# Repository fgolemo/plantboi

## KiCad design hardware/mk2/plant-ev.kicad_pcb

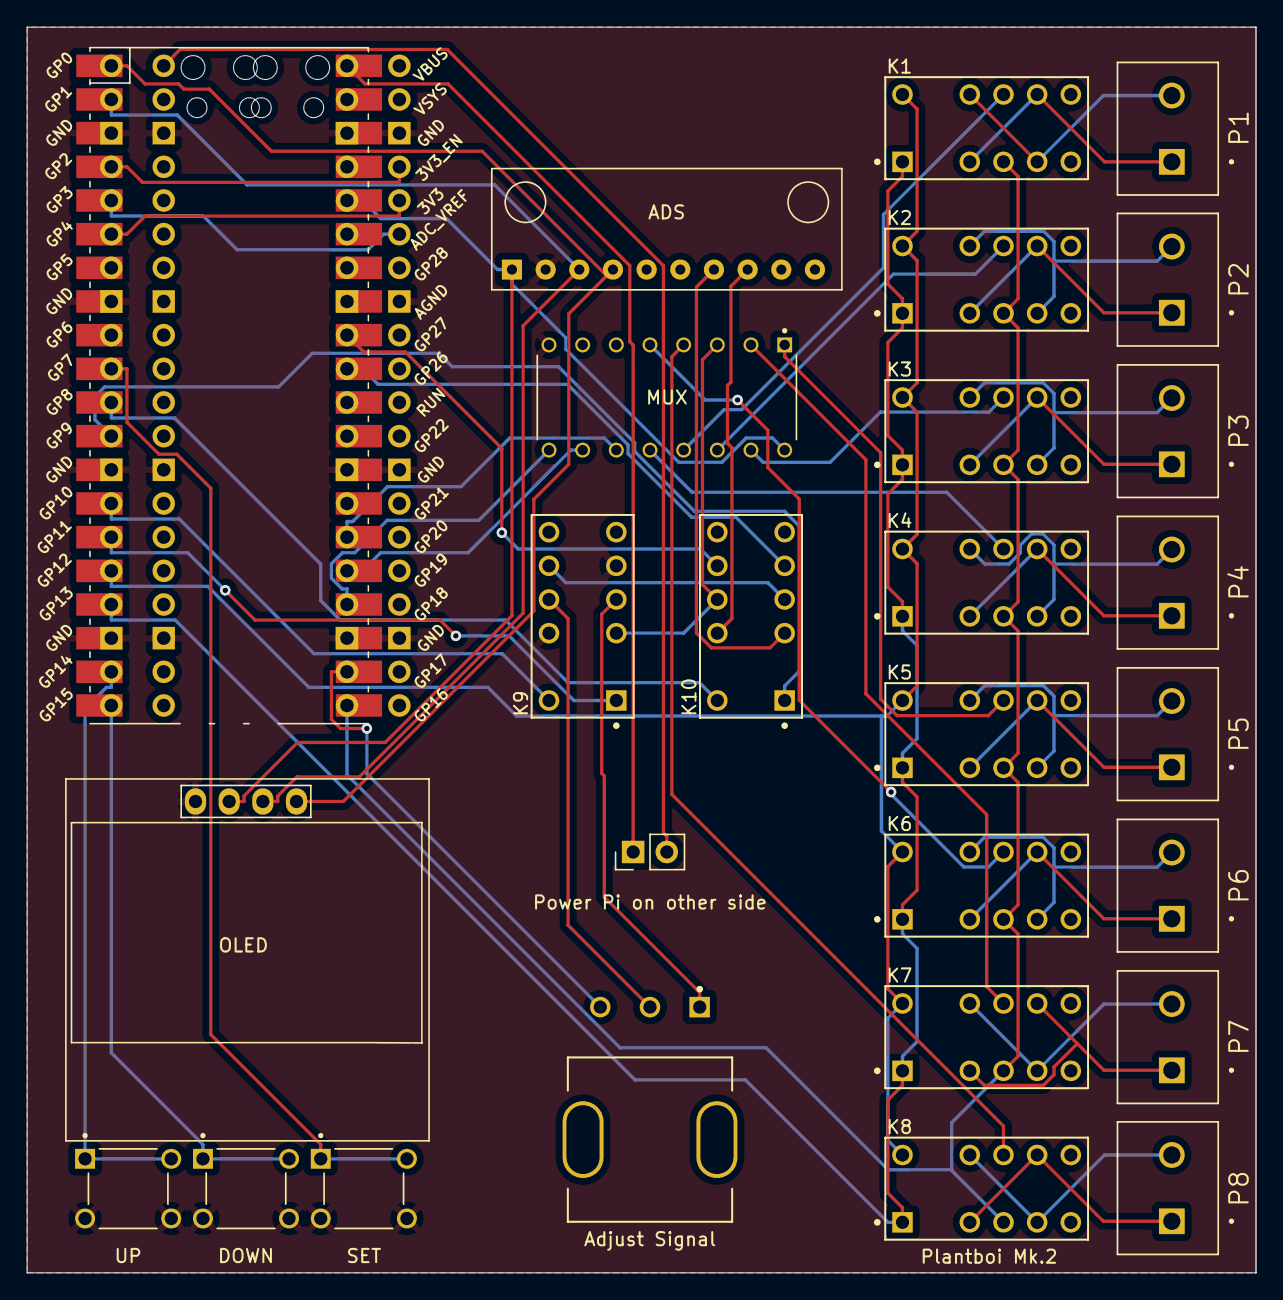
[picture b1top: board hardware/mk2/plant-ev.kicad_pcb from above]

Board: 2 copper layers, 92.7 x 94.0 mm, 28 parts (1 on the bottom side), 55 nets.

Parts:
ADS: ADS1115_ADC_Module; ADC1115_ADC_Module
Adjust Signal: PDB12-H4301-105BF; Bourns-PDB12-H4301-105BF-0
DOWN: TS02-66-120-BK-160-LCR-D; SW_TS02-66-120-BK-160-LCR-D
K1, K2, K3, K4, K5, K6, K7, K8, K9, K10: TXS2-L-3V; Panasonic-TXS2-L-3V-MFG
MUX: CD74HC4051E; DIP794W45P254L1969H508Q16
OLED: SSD1306; 128x64OLED
P1, P2, P3, P4, P5, P6, P7, P8: TB002-500-02BE; CUI_TB002-500-02BE
Power Pi on other side: Jumper_2_Open; PinHeader_1x02_P2.54mm_Vertical
SET: TS02-66-120-BK-160-LCR-D; SW_TS02-66-120-BK-160-LCR-D
U1: Pico influx; RPi_Pico_SMD_TH_NOGVE
U2: Pico sensor; RPi_Pico_SMD_TH_NOGVE
UP: TS02-66-120-BK-160-LCR-D; SW_TS02-66-120-BK-160-LCR-D

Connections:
/3V: ADS.1 (VCC), MUX.16 (VCC), OLED.2 (VCC), U2.36 (3V3)
/ADC1: K10.5, U2.31 (GPIO26_ADC0)
/ADC2: K10.8, U2.32 (GPIO27_ADC1)
/GND: ADS.2 (GND), DOWN.3, DOWN.4, K9.5, K9.10, MUX.8 (GND), OLED.1 (GND), SET.3, SET.4, U1.3 (GND), U1.8 (GND), U1.13 (GND), U1.18 (GND), U1.23 (GND), U1.28 (GND), U1.38 (GND), U2.3 (GND), U2.8 (GND), U2.13 (GND), U2.18 (GND), U2.23 (GND), U2.28 (GND), U2.38 (GND), UP.3, UP.4
/MUX0: MUX.11 (S0), U2.26 (GPIO20)
/MUX1: MUX.10 (S1), U2.25 (GPIO19)
/MUX2: MUX.9 (S2), U2.24 (GPIO18)
/POTP: Adjust Signal.3, U2.22 (GPIO17)
/PRBE: K1.4, K2.4, K3.4, K4.4, K5.4, K6.4, K7.4, K8.4, U2.21 (GPIO16)
/R1M: K1.1 (SET+), K2.1 (SET+), K3.1 (SET+), K4.1 (SET+), K5.1 (SET+), K6.1 (SET+), K7.1 (SET+), K8.1 (SET+), U2.17 (GPIO13)
/R1P: K1.12 (RESET+), K2.12 (RESET+), K3.12 (RESET+), K4.12 (RESET+), K5.12 (RESET+), K6.12 (RESET+), K7.12 (RESET+), K8.12 (RESET+), U2.16 (GPIO12)
/R2M: K9.1 (SET+), U2.15 (GPIO11)
/R2P: K9.12 (RESET+), U2.14 (GPIO10)
/R3M: K10.1 (SET+), U2.12 (GPIO9)
/R3P: K10.12 (RESET+), U2.11 (GPIO8)
/SCL: ADS.3 (SCL), OLED.3 (SCL), U2.2 (GPIO1)
/SDA: ADS.4 (SDA), OLED.4 (SDA), U2.1 (GPIO0)
unnamed: ADS.7 (A0), K10.3
unnamed: ADS.8 (A1), K10.10
unnamed: K1.3, K1.8, P1.1
unnamed: K1.5, K1.10, P1.2
unnamed: K2.3, K2.8, P2.1
unnamed: K2.5, K2.10, P2.2
unnamed: K3.3, K3.8, P3.1
unnamed: K3.5, K3.10, P3.2
unnamed: K4.3, K4.8, P4.1
unnamed: K4.5, K4.10, P4.2
unnamed: K5.3, K5.8, P5.1
unnamed: K5.5, K5.10, P5.2
unnamed: K6.3, K6.8, P6.1
unnamed: K6.5, K6.10, P6.2
unnamed: K7.3, K7.8, P7.1
unnamed: K7.5, K7.10, P7.2
unnamed: K8.3, K8.8, P8.1
unnamed: K8.5, K8.10, P8.2
unnamed: Power Pi on other side.1 (A), U2.40 (VBUS)
unnamed: Power Pi on other side.2 (B), U1.40 (VBUS)
unnamed: Adjust Signal.1, K9.4
unnamed: Adjust Signal.2, K9.9
unnamed: K9.8, K10.4
unnamed: U1.4 (GPIO2), U2.4 (GPIO2)
unnamed: U1.5 (GPIO3), U2.6 (GPIO4)
unnamed: U1.6 (GPIO4), U2.5 (GPIO3)
unnamed: SET.1, SET.2, U2.10 (GPIO7)
unnamed: U2.19 (GPIO14), UP.1, UP.2
unnamed: DOWN.1, DOWN.2, U2.20 (GPIO15)
unnamed: K1.9, MUX.13 (A0)
unnamed: K2.9, MUX.14 (A1)
unnamed: K3.9, MUX.15 (A2)
unnamed: K4.9, MUX.12 (A3)
unnamed: K5.9, MUX.1 (A4)
unnamed: K6.9, MUX.5 (A5)
unnamed: K7.9, MUX.2 (A6)
unnamed: K8.9, MUX.4 (A7)
unnamed: K9.3, K10.9, MUX.3 (SIG)

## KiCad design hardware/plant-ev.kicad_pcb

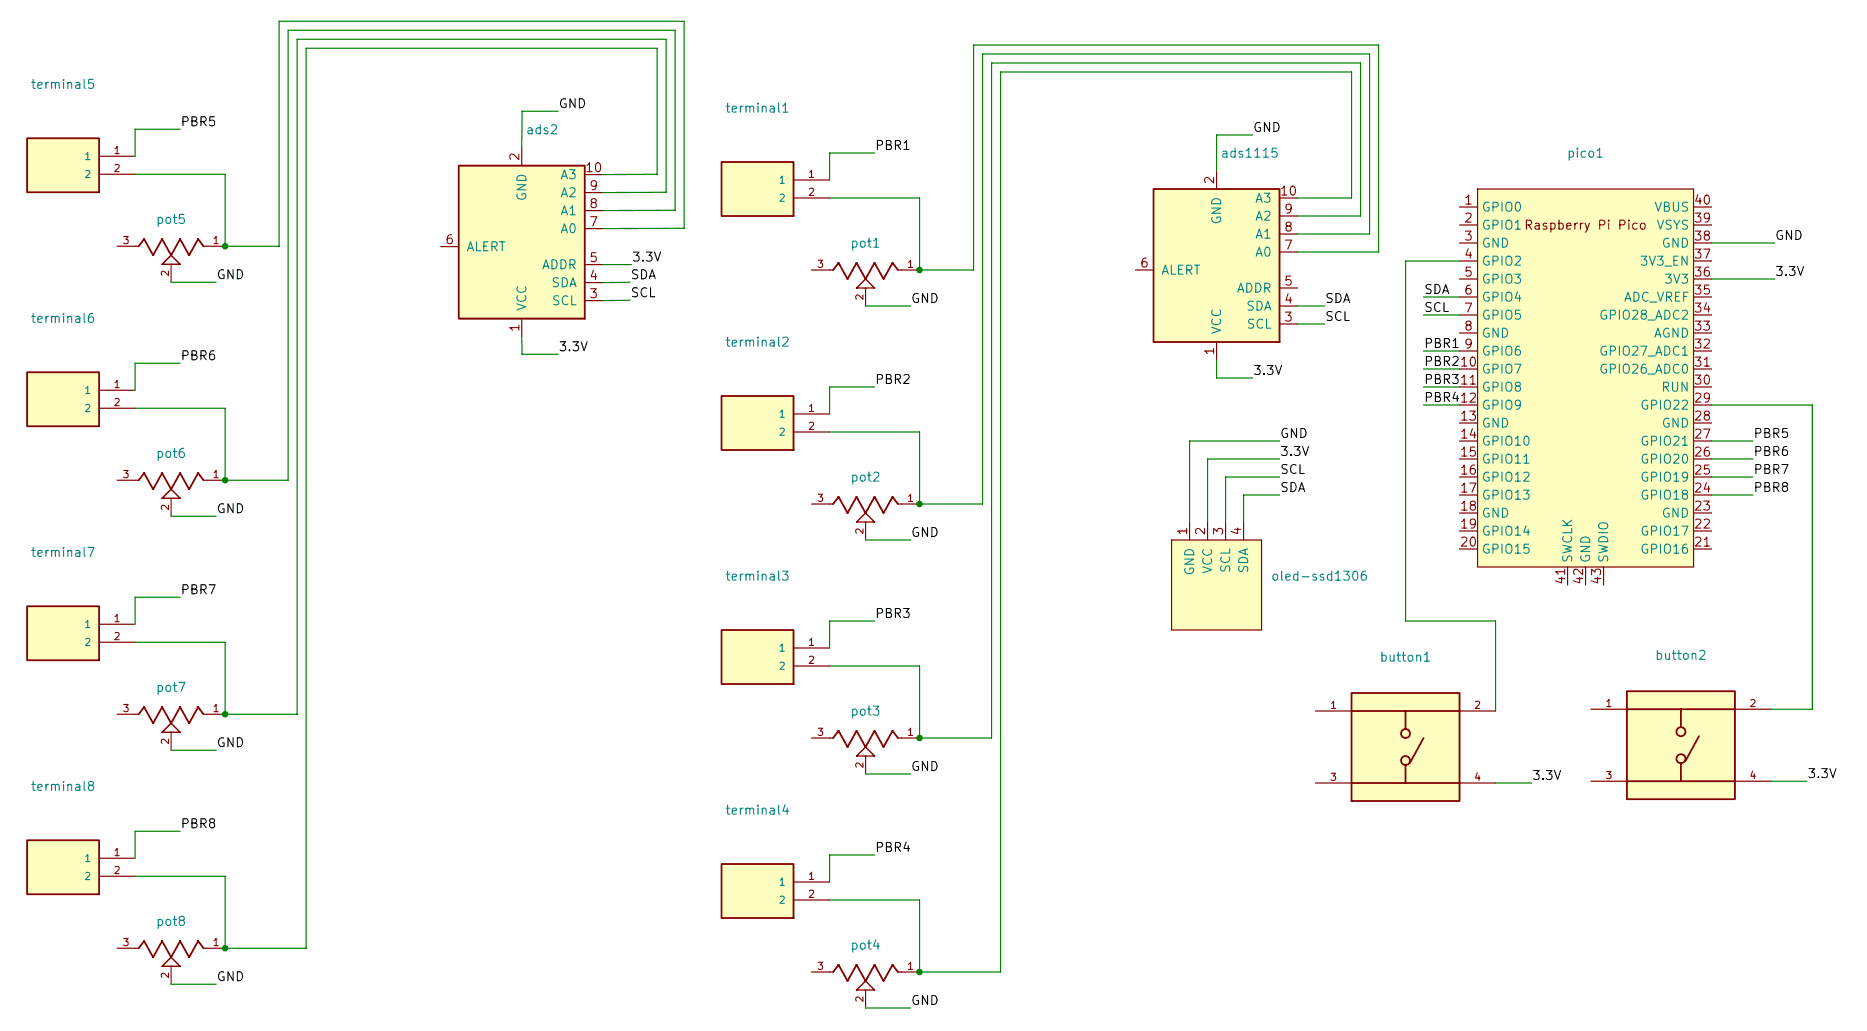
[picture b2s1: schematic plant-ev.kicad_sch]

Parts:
ads2, ads1115: ADS1115_ADC_Module; ADC1115_ADC_Module
button1, button2: TS02-66-120-BK-160-LCR-D; SW_TS02-66-120-BK-160-LCR-D; PARTREV 1.0
oled-ssd1306: SSD1306; 128x64OLED
pico1: Pico; RPi_Pico_SMD_TH
pot1, pot2, pot3, pot4, pot5, pot6, pot7, pot8: PT01-B120D-A104; TRIM_PT01-B120D-A104; PARTREV 1.0
terminal1, terminal2, terminal3, terminal4, terminal5, terminal6, terminal7, terminal8: TB002-500-02BE; CUI_TB002-500-02BE

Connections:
/3.3V: ads2.1 (VCC), ads2.5 (ADDR), ads1115.1 (VCC), button1.4, button2.4, oled-ssd1306.2 (VCC), pico1.36 (3V3); also elsewhere on the board
/GND: ads2.2 (GND), ads1115.2 (GND), oled-ssd1306.1 (GND), pico1.38 (GND), pot1.2, pot2.2, pot3.2, pot4.2, pot5.2, pot6.2, pot7.2, pot8.2; also elsewhere on the board
/PBR1: pico1.9 (GPIO6), terminal1.1
/PBR2: pico1.10 (GPIO7), terminal2.1
/PBR3: pico1.11 (GPIO8), terminal3.1
/PBR4: pico1.12 (GPIO9), terminal4.1
/PBR5: pico1.27 (GPIO21), terminal5.1
/PBR6: pico1.26 (GPIO20), terminal6.1
/PBR7: pico1.25 (GPIO19), terminal7.1
/PBR8: pico1.24 (GPIO18), terminal8.1
/SCL: ads2.3 (SCL), ads1115.3 (SCL), oled-ssd1306.3 (SCL), pico1.7 (GPIO5); also elsewhere on the board
/SDA: ads2.4 (SDA), ads1115.4 (SDA), oled-ssd1306.4 (SDA), pico1.6 (GPIO4); also elsewhere on the board
unnamed 12: ads1115.7 (A0), pot1.1, terminal1.2; also elsewhere on the board
unnamed 13: ads1115.8 (A1), pot2.1, terminal2.2; also elsewhere on the board
unnamed 14: ads1115.9 (A2), pot3.1, terminal3.2; also elsewhere on the board
unnamed 15: ads1115.10 (A3), pot4.1, terminal4.2; also elsewhere on the board
unnamed: button1.2, pico1.4 (GPIO2)
unnamed: button2.2, pico1.29 (GPIO22)
unnamed: ads2.7 (A0), pot5.1, terminal5.2
unnamed: ads2.8 (A1), pot6.1, terminal6.2
unnamed: ads2.9 (A2), pot7.1, terminal7.2
unnamed: ads2.10 (A3), pot8.1, terminal8.2

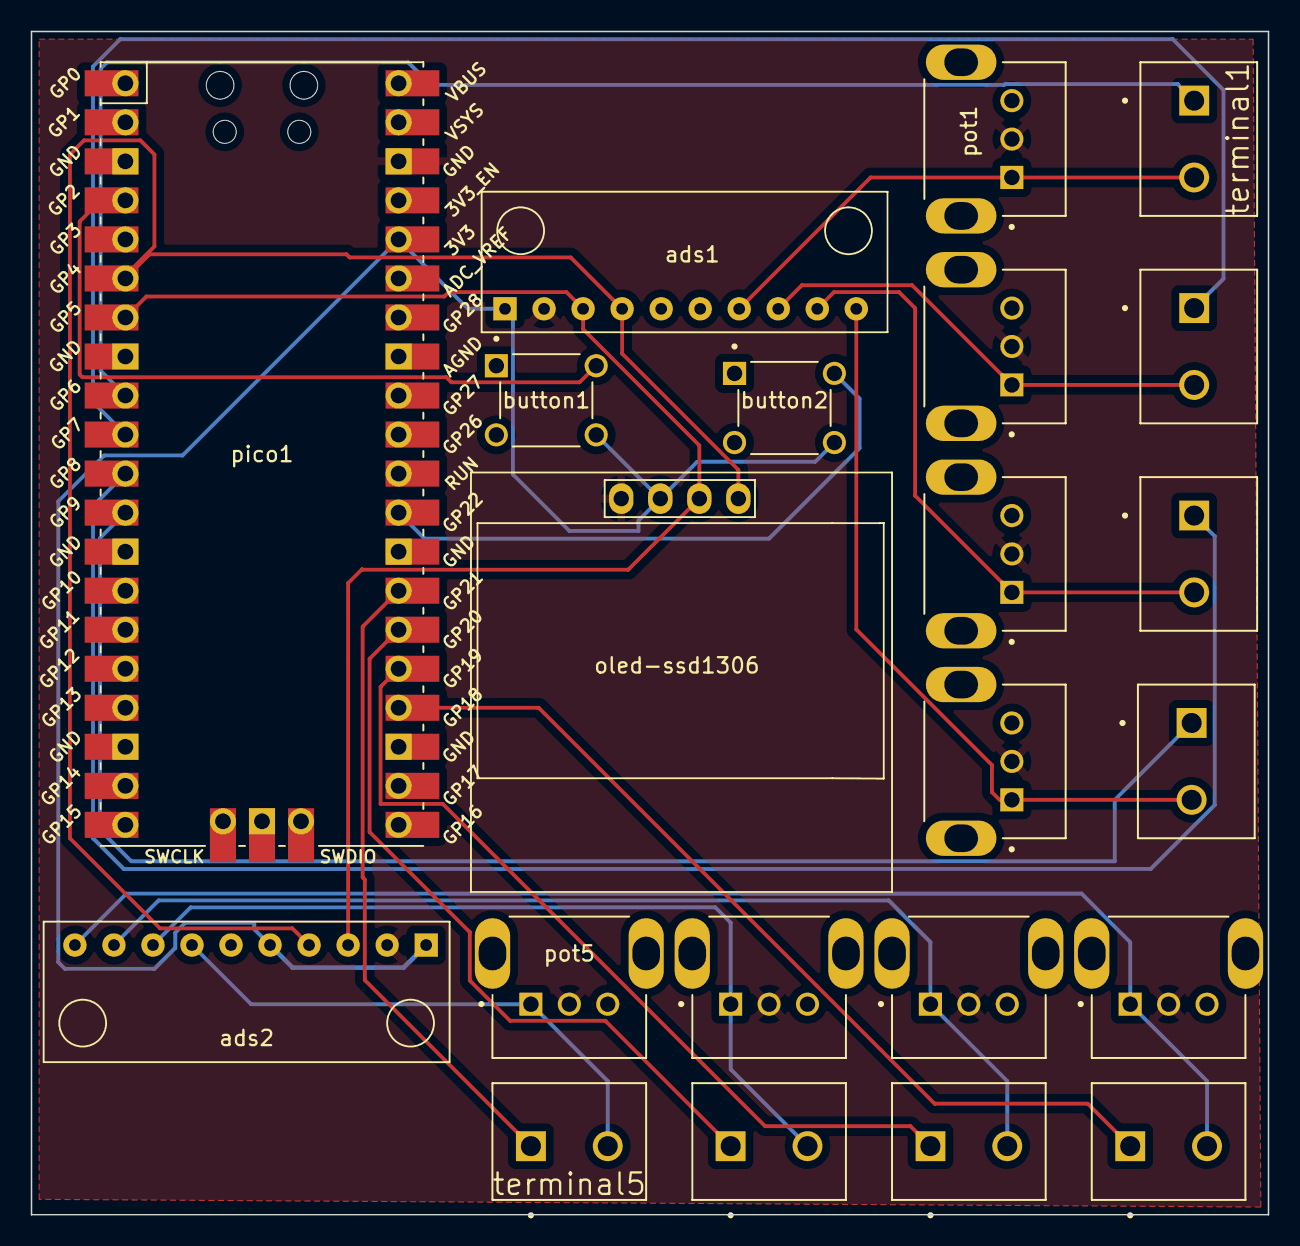
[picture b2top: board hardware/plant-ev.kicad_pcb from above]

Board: 2 copper layers, 80.5 x 77.0 mm, 22 parts (0 on the bottom side), 22 nets.

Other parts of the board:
ads1: ADS1115_ADC_Module; ADC1115_ADC_Module

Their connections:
/3.3V: ads1.1 (VCC); also elsewhere on the board
/GND: ads1.2 (GND); also elsewhere on the board
/SCL: ads1.3 (SCL); also elsewhere on the board
/SDA: ads1.4 (SDA); also elsewhere on the board
unnamed 12: ads1.7 (A0); also elsewhere on the board
unnamed 13: ads1.8 (A1); also elsewhere on the board
unnamed 14: ads1.9 (A2); also elsewhere on the board
unnamed 15: ads1.10 (A3); also elsewhere on the board

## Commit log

2023-04-06 init with working prototype
2023-04-19 sensor data collection that batches and sends to other pico
2023-04-19 lib file
2023-04-19 receives via serial batched data and sends to influx
2023-04-19 lib folders needed
2023-04-19 lib needed for pico
2023-04-19 refactored
2023-05-02 platboi mk.1.5 working code and plantboi mk.2 board
